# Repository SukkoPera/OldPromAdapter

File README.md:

# OldPromAdapter
OldPromAdapter is an Open Hardware Adapter that allows replacing 82s126, 82s129 and 82s131 PROMs with 27512 (E)EPROMs.

## Summary
This is just my remake of [a board by patzik](https://www.ukvac.com/forum/threads/82s126-82s129-82s131-adapter-board-and-82s123.71784/). As far as I can understand, it was meant to replace those PROMs that are often used on Arcade PCBs when they fail. It's already hard to find blank versions of the original PROMs, but finding the programmer that they require is next to impossible (Update: [not anymore](https://github.com/Franck78/BIPOLAR-PROM-PROG)), so having an alternative can be handy.

I was working with Jani on making a reproduction of the Action Replay cartridge for the C64, which has an 82s129 onboard and we needed some way to dump it. We found patzik's adapter but I didn't like the fact that it forces the unused data lines to ground. The data lines are outputs for the EPROM and they should be left disconnected if not used. It probably won't make much difference if you set the unused bits to 0, bit bad things will happen if you forget that and set any to 1. So I just redesigned the adapter and left them disconnected.

I also think that having the adapter design files available for modification can be very useful, as those PROMs are much smaller than a 27512 EPROM and the adapter is necessarily a bit clunky in its current form. Thus it might not fit everywhere, but with the KiCad project at hand it can be quickly modified to fit in more places, if not everywhere. This is just another example of why "design files" is better than "free gerbers" and of why the latter does not match the *open source* paradigm, even though many people still won't get it.

The adapter works perfectly with Winbond W27C512 EEPROMs, which can be found very easily and for little money and which can be programmed with the ubiquitous TL866 programmer.

One thing to keep in mind is that while the PROMs in question are much faster than the W27C512 (10 vs 50 ns, as a rule of thumb), that speed is not necessarily *required* wherever those PROMs were used. If you have a circuit that requires the speed, though, the adapter just won't work reliably.

## License
The OldPromAdapter documentation, including the design itself, is copyright &copy; SukkoPera 2022 and is licensed under the [Creative Commons Attribution-NonCommercial-ShareAlike 4.0 International License](https://creativecommons.org/licenses/by-nc-sa/4.0/).

This documentation is distributed *as is* and WITHOUT ANY EXPRESS OR IMPLIED WARRANTIES whatsoever with respect to its functionality, operability or use, including, without limitation, any implied warranties OF MERCHANTABILITY, SATISFACTORY QUALITY, FITNESS FOR A PARTICULAR PURPOSE or infringement. We expressly disclaim any liability whatsoever for any direct, indirect, consequential, incidental or special damages, including, without limitation, lost revenues, lost profits, losses resulting from business interruption or loss of data, regardless of the form of action or legal theory under which the liability may be asserted, even if advised of the possibility or likelihood of such damages.

The bottom line is: you are free to make PCBs for yourself and give your excess away **at cost**, but you are **not allowed to sell** these boards for profit.

## Support the Project
If you want to get boards, you can get them made from PCBWay through this link:

You get my gratitude and cheap, professionally-made and good quality PCBs, I get some credit that will help with this and [other projects](https://www.pcbway.com/project/member/shareproject/?bmbid=41100). You won't even have to worry about the various PCB options, it's all pre-configured for you!

Also, if you still have to register, [you can use this link](https://www.pcbway.com/setinvite.aspx?inviteid=41100) to get some bonus initial credit (and yield me some more).

You can also buy me a coffee if you want:

## Thanks
- patzik for the original idea.
- [Jani](http://blog.worldofjani.com) for being an awesome guy.

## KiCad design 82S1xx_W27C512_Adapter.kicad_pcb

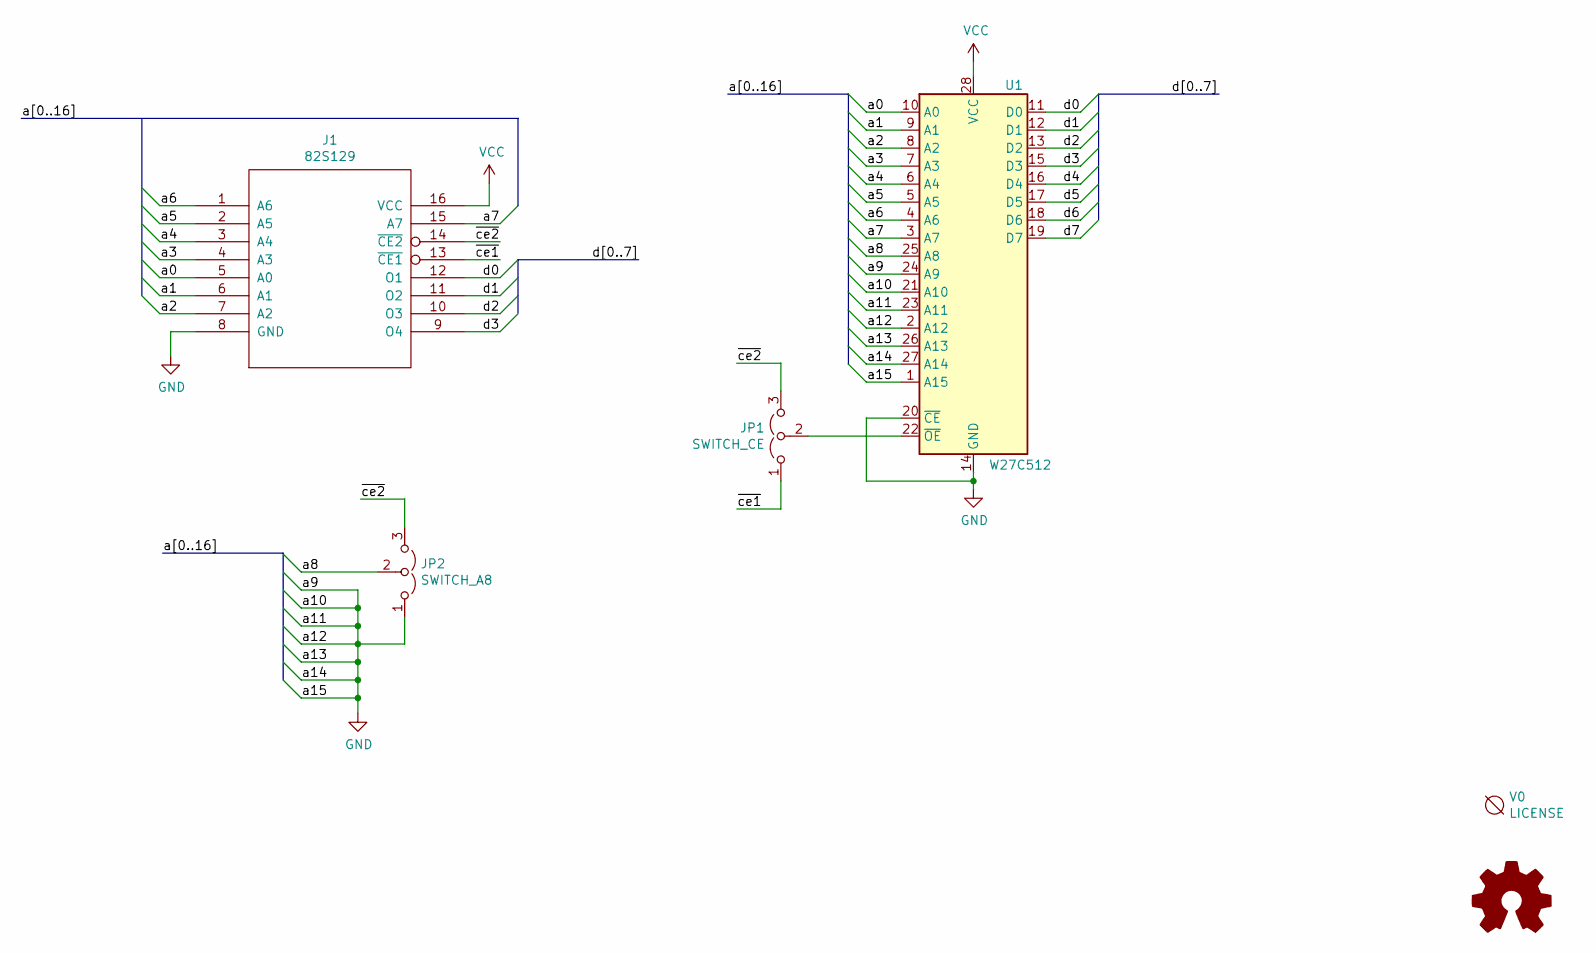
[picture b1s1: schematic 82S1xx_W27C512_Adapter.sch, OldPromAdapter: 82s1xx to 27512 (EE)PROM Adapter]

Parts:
J1: 82S129; DIP-16_W7.62mm_Plug
JP1: SWITCH_CE; SolderJumper-3
JP2: SWITCH_A8; SolderJumper-3
U1: W27C512; DIP-28_W15.24mm_Socket_LongPads
V0: LICENSE; cc_by_nc_sa

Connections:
/a0: J1.5 (A0), U1.10 (A0)
/a1: J1.6 (A1), U1.9 (A1)
/a2: J1.7 (A2), U1.8 (A2)
/a3: J1.4 (A3), U1.7 (A3)
/a4: J1.3 (A4), U1.6 (A4)
/a5: J1.2 (A5), U1.5 (A5)
/a6: J1.1 (A6), U1.4 (A6)
/a7: J1.15 (A7), U1.3 (A7)
/a8: JP2.2 (C), U1.25 (A8)
/d0: J1.12 (O1), U1.11 (D0)
/d1: J1.11 (O2), U1.12 (D1)
/d2: J1.10 (O3), U1.13 (D2)
/d3: J1.9 (O4), U1.15 (D3)
/d4: U1.16 (D4)
/d5: U1.17 (D5)
/d6: U1.18 (D6)
/d7: U1.19 (D7)
/~ce1: J1.13 (~CE1), JP1.1 (A)
/~ce2: J1.14 (~CE2), JP1.3 (B), JP2.3 (B)
GND: J1.8 (GND), JP2.1 (A), U1.1 (A15), U1.2 (A12), U1.14 (GND), U1.20 (~CE), U1.21 (A10), U1.23 (A11), U1.24 (A9), U1.26 (A13), U1.27 (A14)
unnamed: JP1.2 (C), U1.22 (~OE)
VCC: J1.16 (VCC), U1.28 (VCC)

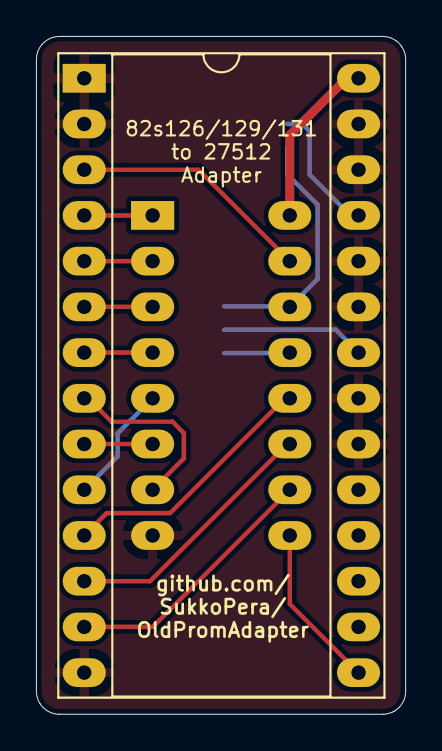
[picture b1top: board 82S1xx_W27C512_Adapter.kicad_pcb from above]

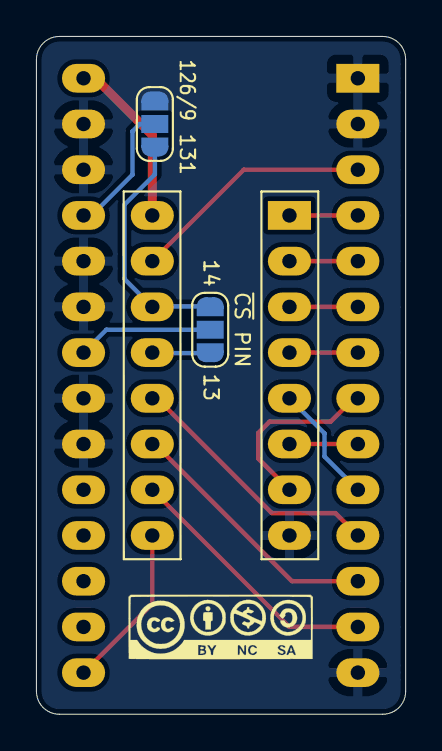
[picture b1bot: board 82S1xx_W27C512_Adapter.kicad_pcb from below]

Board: 2 copper layers, 20.5 x 37.7 mm, 5 parts (3 on the bottom side), 18 nets.

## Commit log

2021-12-23 Initial import
2021-12-27 Ready for V1
2022-02-27 Add license, ready for V1 and go-public
2022-02-27 Add renders
2022-02-27 Fix image path
2022-02-27 Add social image
2022-02-28 Add PCBWay link
2024-09-18 Fix URL in README
2024-09-18 *Really* fix URL...

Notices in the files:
82S1xx_W27C512_Adapter.kicad_pcb:
Licensed under CC BY-NC-SA 4.0
